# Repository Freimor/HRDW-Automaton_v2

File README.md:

## HRDW-Automaton v2
Automaton v2 is a version of [HID Key](https://github.com/Freimor/HRDW-HIDKey) tuned for staff of the ANO "School 21". Main reason for redesign is changing a microcontroller to RP2040. Additional feature - you can choose type of USB connector (Male or Female) before soldering.
### Notes
- Side buttons is cool with additional plate
- Ability to choose USB type - ok, but not usable footprint must be covered by 3d printed case or elecrically isolated from circuit with 0 resistors.
- Case with glued window - NOT GOOD. Unreasonable assembly step.
- DON'T MESSED UP WITH CORE VOLTAGE!!! (1v1)

The project is completed in Q2 2023.

## Parameters for PCB order
4 layer board

0.8mm thickness

0.3mm min hole size

BOM list in HTML file named BOM

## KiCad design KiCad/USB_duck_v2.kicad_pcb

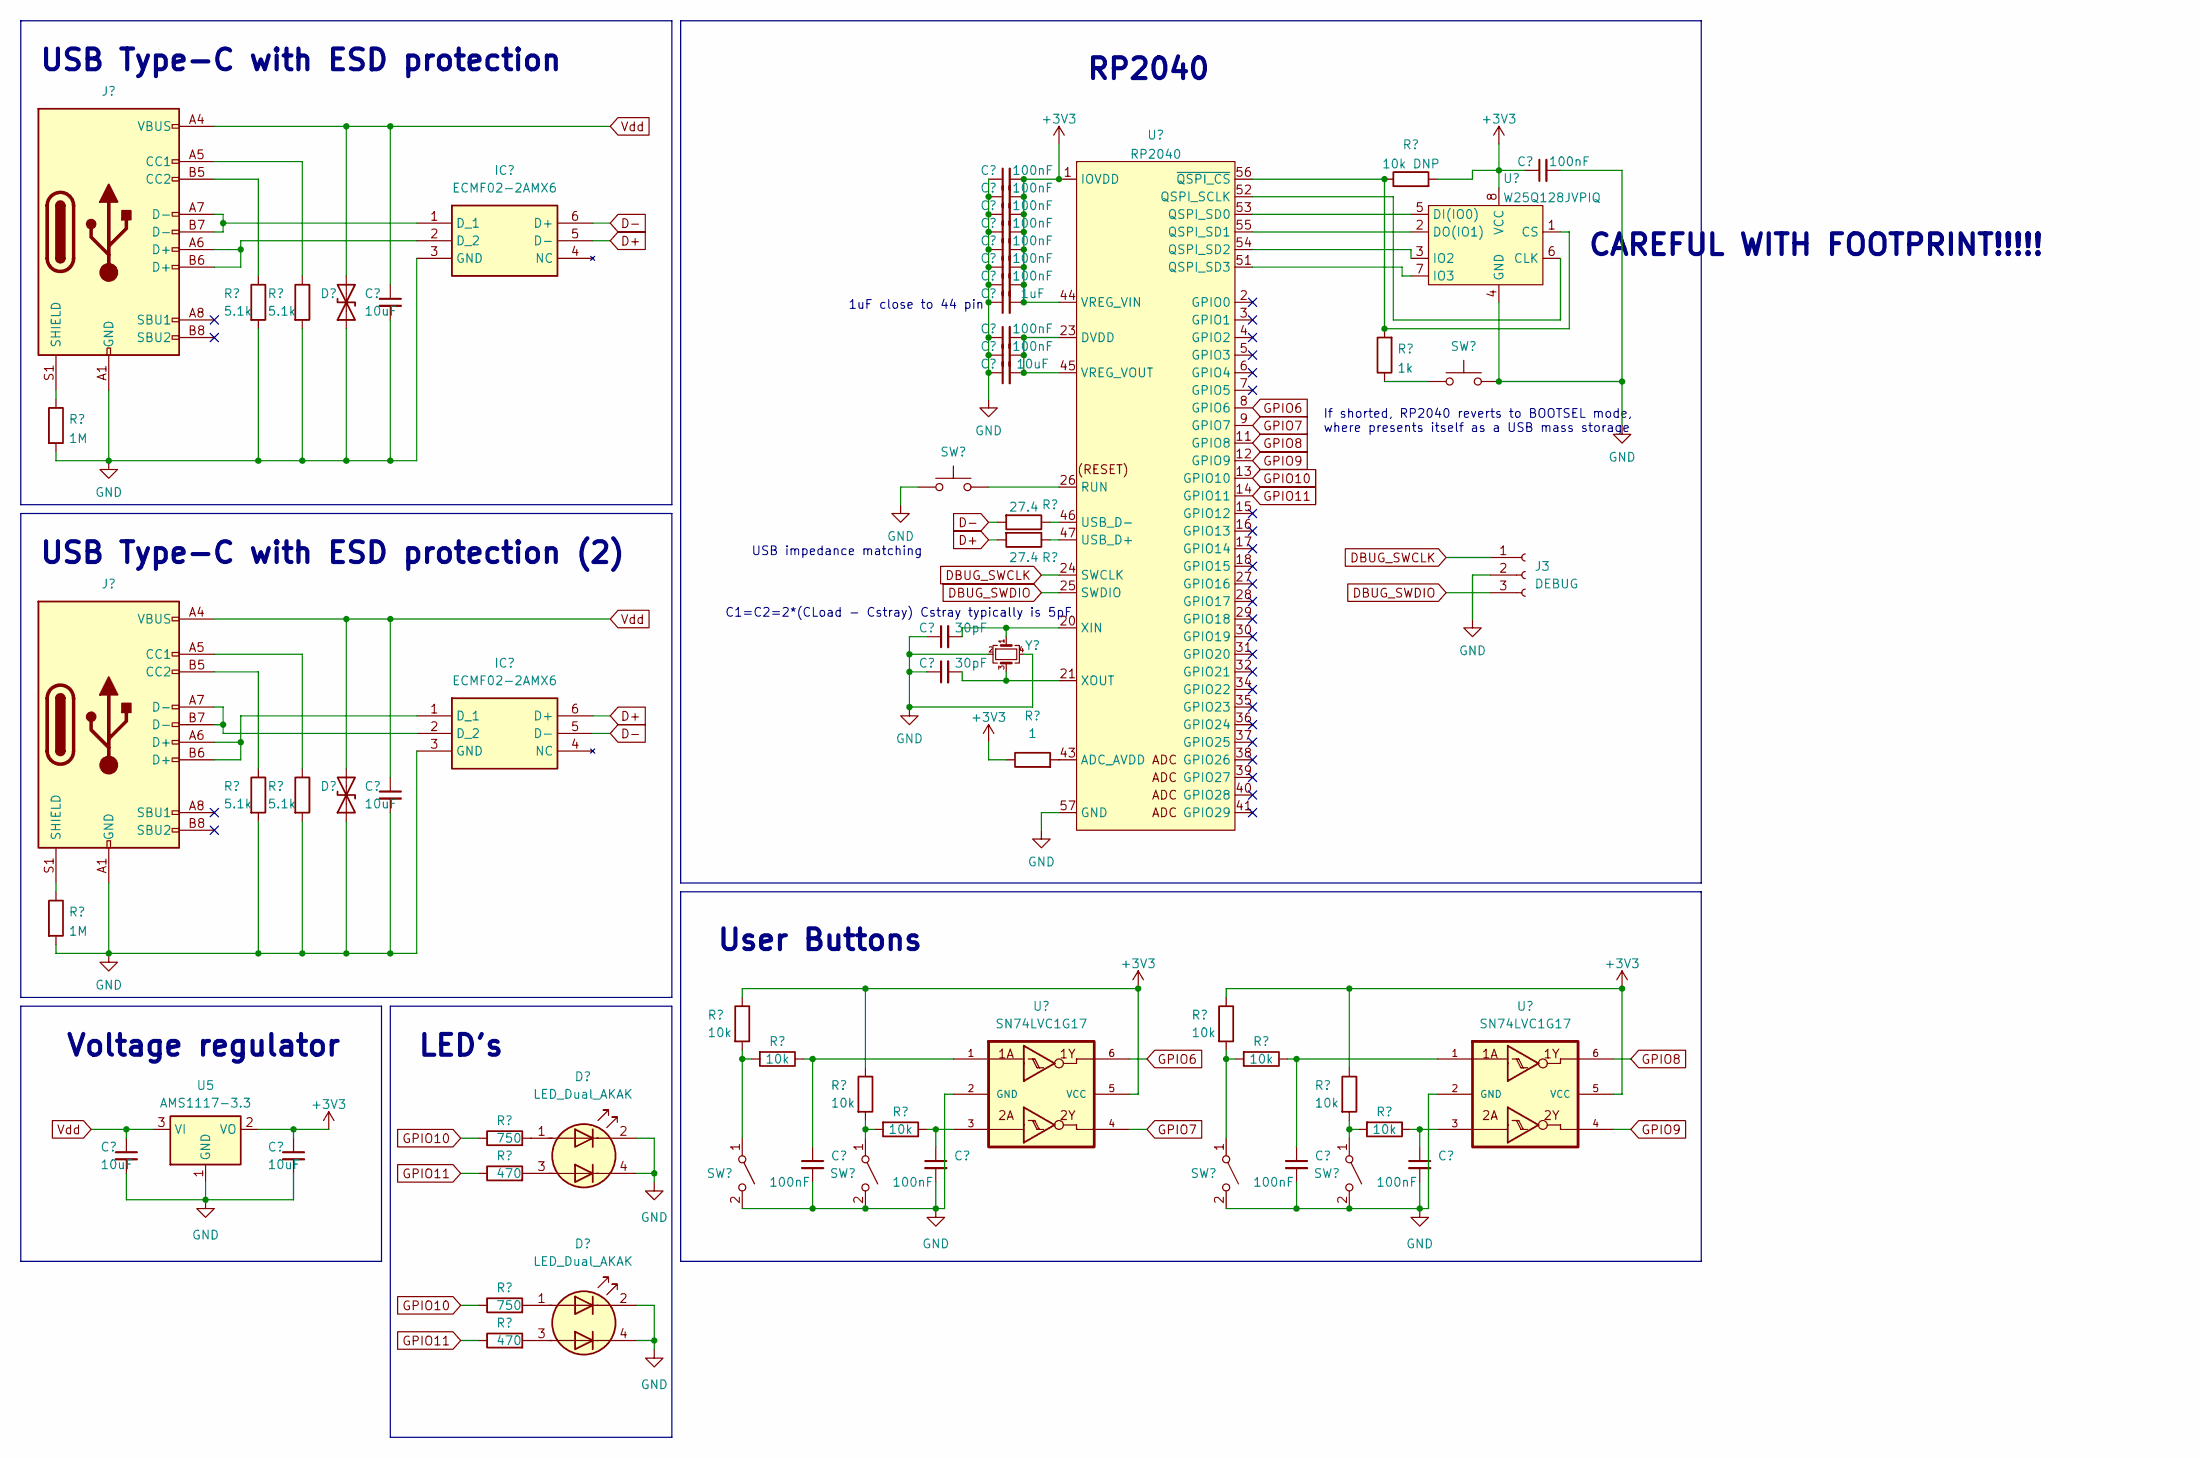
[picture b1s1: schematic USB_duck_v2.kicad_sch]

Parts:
BOOTSEL1: BOOTSEL; SW_SMD_XKB_(TS-1809SM-C)
C1, C2, C3, C4, C5, C6, C7, C8, C11, C12, C19, C20, C21, C22: 100nF; C_0402_1005Metric
C9, C13, C16, C17, C18: 10uF; C_0603_1608Metric
C10: 1uF; C_0603_1608Metric
C14, C15: 30pF; C_0402_1005Metric
D1, D2: D_TVS; ESD_PGB1010603MR
D3, D4: LED_Dual_AKAK; LED_RG_KPB-3025
IC1, IC2: ECMF02-2AMX6; ESD_ECMF02-2AMX6; Manufacturer_Part_Number ECMF02-2AMX6; Mouser Part Number 511-ECMF02-2AMX6
J1: USB_C_Receptacle_USB2.0; XKB_TYPE-C-U261-241N-4BS60
J2: USB_C_Receptacle_USB2.0; GCT_TYPE-C-USB4505-03-0-A
J3: DEBUG; PinHeader_1x03_P1.00mm_Vertical
R1: 10k DNP; R_0402_1005Metric
R2, R3, R9, R10: 5.1k; R_0402_1005Metric
R4: 1k; R_0402_1005Metric
R5, R11: 1M; R_0402_1005Metric
R6, R7: 27.4; R_0402_1005Metric
R8: 1; R_0402_1005Metric
R12, R13, R14, R15, R16, R17, R18, R19: 10k; R_0402_1005Metric
R20, R22: 750; R_0402_1005Metric
R21, R23: 470; R_0402_1005Metric
SW1: SW_Push; SW_SMD_XKB_(TS-1809SM-C)
SW2, SW3, SW4, SW5: SW_SPST; SW_SMD_KLS7-TS5401
U1: RP2040; MK_RP2040
U2: W25Q128JVPIQ; FLASH_W25Q128JVPIQ
U3, U4: SN74LVC1G17; SOT-23-6
U5: AMS1117-3.3; SOT-89-3
Y1: Crystal_GND24_Small; Crystal_SMD_3225-4Pin_3.2x2.5mm

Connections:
+3V3: C1.1, C2.2, C3.2, C4.2, C5.2, C6.2, C7.2, C8.2, C10.2, C18.1, R1.2, R8.1, R12.1, R13.1, R16.1, R17.1, U1.1 (IOVDD), U1.10 (IOVDD), U1.22 (IOVDD), U1.33 (IOVDD), U1.42 (IOVDD), U1.44 (VREG_VIN), U1.48 (USB_VDD), U1.49 (IOVDD), U2.8 (VCC), U3.5 (VCC), U4.5 (VCC), U5.2 (VO)
D+: IC1.5 (D-), IC2.6 (D+), R7.2
D-: IC1.6 (D+), IC2.5 (D-), R6.2
DBUG_SWCLK: J3.1, U1.24 (SWCLK)
DBUG_SWDIO: J3.3, U1.25 (SWDIO)
GND: BOOTSEL1.2, C1.2, C2.1, C3.1, C4.1, C5.1, C6.1, C7.1, C8.1, C9.2, C10.1, C11.1, C12.1, C13.1, C14.1, C15.1, C16.2, C17.2, C18.2, C19.2, C20.2, C21.2, C22.2, D1.1 (A1), D2.1 (A1), D3.2 (K1), D3.4 (K2), D4.2 (K1), D4.4 (K2), IC1.3 (GND), IC2.3 (GND), J1.A1 (GND), J1.A12 (GND), J1.B1 (GND), J1.B12 (GND), J2.A1 (GND), J2.A12 (GND), J2.B1 (GND), J2.B12 (GND), J3.2, R2.2, R3.2, R5.2, R9.2, R10.2, R11.2, SW1.1, SW2.2 (B), SW3.2 (B), SW4.2 (B), SW5.2 (B), U1.19 (TESTEN), U1.57 (GND), U2.4 (GND), U3.2 (GND), U4.2 (GND), U5.1 (GND), Y1.2, Y1.4; also elsewhere on the board
GPIO6: U1.8 (GPIO6), U3.6
GPIO7: U1.9 (GPIO7), U3.4
GPIO8: U1.11 (GPIO8), U4.6
GPIO9: U1.12 (GPIO9), U4.4
GPIO10: R20.1, R22.1, U1.13 (GPIO10)
GPIO11: R21.1, R23.1, U1.14 (GPIO11)
unnamed: BOOTSEL1.1, R4.1
unnamed: C19.1, R14.1, U3.1
unnamed: C20.1, R18.1, U3.3
unnamed: C21.1, R15.1, U4.1
unnamed: C22.1, R19.1, U4.3
unnamed: D3.1 (A1), R20.2
unnamed: D3.3 (A2), R21.2
unnamed: D4.1 (A1), R22.2
unnamed: D4.3 (A2), R23.2
unnamed: IC1.1 (D_1), J1.A7 (D-), J1.B7 (D-)
unnamed: IC1.2 (D_2), J1.A6 (D+), J1.B6 (D+)
unnamed: IC2.1 (D_1), J2.A6 (D+), J2.B6 (D+)
unnamed: IC2.2 (D_2), J2.A7 (D-), J2.B7 (D-)
unnamed: J1.A5 (CC1), R3.1
unnamed: J1.B5 (CC2), R2.1
unnamed: J1.S1 (SHIELD), R5.1
unnamed: J2.A5 (CC1), R10.1
unnamed: J2.B5 (CC2), R9.1
unnamed 30: J2.S1 (SHIELD), R11.1; also elsewhere on the board
unnamed: R12.2, R14.2, SW2.1 (A)
unnamed: R16.2, R18.2, SW3.1 (A)
unnamed: R13.2, R15.2, SW4.1 (A)
unnamed: R17.2, R19.2, SW5.1 (A)
unnamed: R8.2, U1.43 (ADC_AVDD)
unnamed: U1.52 (QSPI_SCLK), U2.6 (CLK)
unnamed: U1.53 (QSPI_SD0), U2.5 (DI(IO0))
unnamed: U1.55 (QSPI_SD1), U2.2 (DO(IO1))
unnamed: U1.54 (QSPI_SD2), U2.3 (IO2)
unnamed: U1.51 (QSPI_SD3), U2.7 (IO3)
unnamed: SW1.2, U1.26 (RUN)
unnamed: R7.1, U1.47 (USB_D+)
unnamed: R6.1, U1.46 (USB_D-)
unnamed: C11.2, C12.2, C13.2, U1.23 (DVDD), U1.45 (VREG_VOUT), U1.50 (DVDD)
unnamed: C14.2, U1.20 (XIN), Y1.1
unnamed: C15.2, U1.21 (XOUT), Y1.3
unnamed: R1.1, R4.2, U1.56 (~QSPI_CS), U2.1 (CS)
Vdd: C9.1, C16.1, C17.1, D1.2 (A2), D2.2 (A2), J1.A4 (VBUS), J1.A9 (VBUS), J1.B4 (VBUS), J1.B9 (VBUS), J2.A4 (VBUS), J2.A9 (VBUS), J2.B4 (VBUS), J2.B9 (VBUS), U5.3 (VI)

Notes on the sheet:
USB impedance matching
USB Type-C with ESD protection (2)
USB Type-C with ESD protection
Voltage regulator
LED's
1uF close to 44 pin
If shorted, RP2040 reverts to BOOTSEL mode, where presents itself as a USB mass storage
CAREFUL WITH FOOTPRINT!!!!!
User Buttons
RP2040
C1=C2=2*(CLoad - Cstray) Cstray typically is 5pF

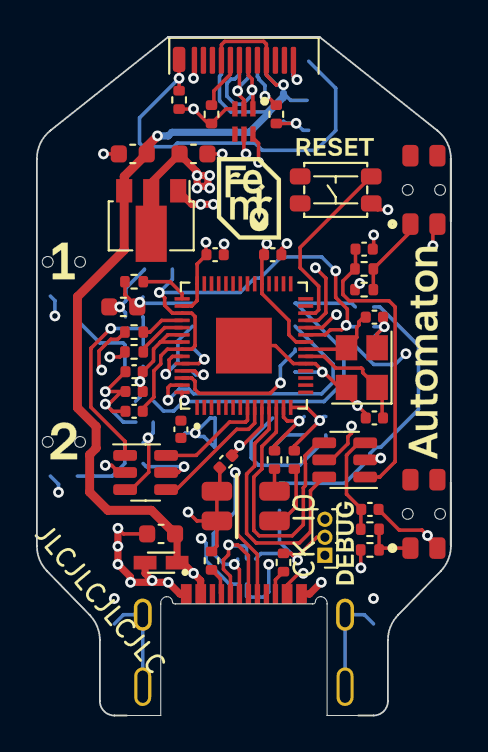
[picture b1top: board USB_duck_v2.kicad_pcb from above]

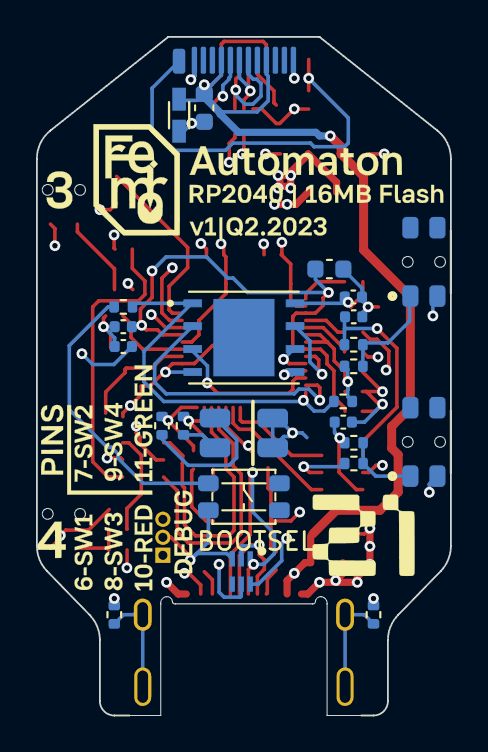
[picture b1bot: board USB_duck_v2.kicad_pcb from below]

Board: 4 copper layers, 23.0 x 37.7 mm, 69 parts (24 on the bottom side), 49 nets.

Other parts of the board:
R11#2: 1M; R_0402_1005Metric
Ref**: Val**; front
Ref**#2: Val**; back

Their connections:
GND: R11#2.2; also elsewhere on the board
unnamed 30: R11#2.1; also elsewhere on the board

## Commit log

2024-11-16 MAIN
